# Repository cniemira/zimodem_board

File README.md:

Hardware for [zimodem](https://github.com/bozimmerman/Zimodem)

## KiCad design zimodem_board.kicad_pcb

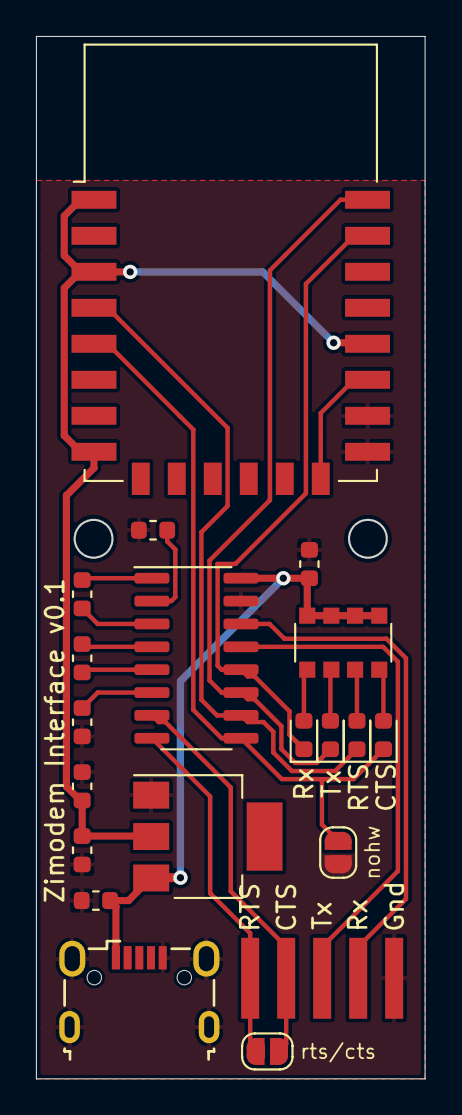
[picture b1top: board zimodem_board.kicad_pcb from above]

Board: 2 copper layers, 21.5 x 57.8 mm, 20 parts (0 on the bottom side), 22 nets.

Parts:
C1, C2: 10uF; C_0603_1608Metric
C3: 100nF; C_0603_1608Metric
C4, C5, C6, C7, C8: 1uF; C_0603_1608Metric
D1, D2, D3, D4: LED; LED_0603_1608Metric
J1: USB_OTG; USB_Micro-B_Wuerth_629105150521
J2: RS232; smd_wire_pads_01x05
JP1: rts/cts; SolderJumper-2_P1.3mm_Open_RoundedPad1.0x1.5mm
JP2: RS232_rts/crs; SolderJumper-2_P1.3mm_Open_RoundedPad1.0x1.5mm
RN1: R_Pack04; R_Array_Convex_4x1206
U1: LM1117-3.3; SOT-223
U2: MAX232; SOIC-16_3.9x9.9mm_P1.27mm
U3: ESP-12E

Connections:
+3V3: C2.1, C3.1, U1.2, U3.1, U3.3, U3.8, U3.18
+5V: C1.1, C5.2, J1.1, RN1.5, RN1.6, RN1.7, RN1.8, U1.3, U2.16
GND: C1.2, C2.2, C3.2, C5.1, C7.2, C8.2, J1.5, J1.6, J2.5, JP2.2, U1.1, U2.15, U3.15, U3.16
unnamed: C4.1, U2.1
unnamed: C4.2, U2.3
unnamed: C6.1, U2.4
unnamed: C6.2, U2.5
unnamed: C7.1, U2.6
unnamed: C8.1, U2.2
unnamed: D1.2, RN1.1
unnamed: D2.2, RN1.2
unnamed: D3.2, RN1.3
unnamed: D4.2, RN1.4
RS232_CTS: J2.2, JP1.2, U2.7
RS232_RTS: J2.1, JP1.1, U2.8
RS232_Rx: J2.4, U2.14
RS232_Tx: J2.3, U2.13
TTL_CTS: D4.1, JP2.1, U2.9, U3.5
TTL_RI: U3.14, U3.17
TTL_RTS: D3.1, U2.10, U3.4
TTL_Rx: D1.1, U2.12, U3.21
TTL_Tx: D2.1, U2.11, U3.22

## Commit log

2019-09-19 initial import
